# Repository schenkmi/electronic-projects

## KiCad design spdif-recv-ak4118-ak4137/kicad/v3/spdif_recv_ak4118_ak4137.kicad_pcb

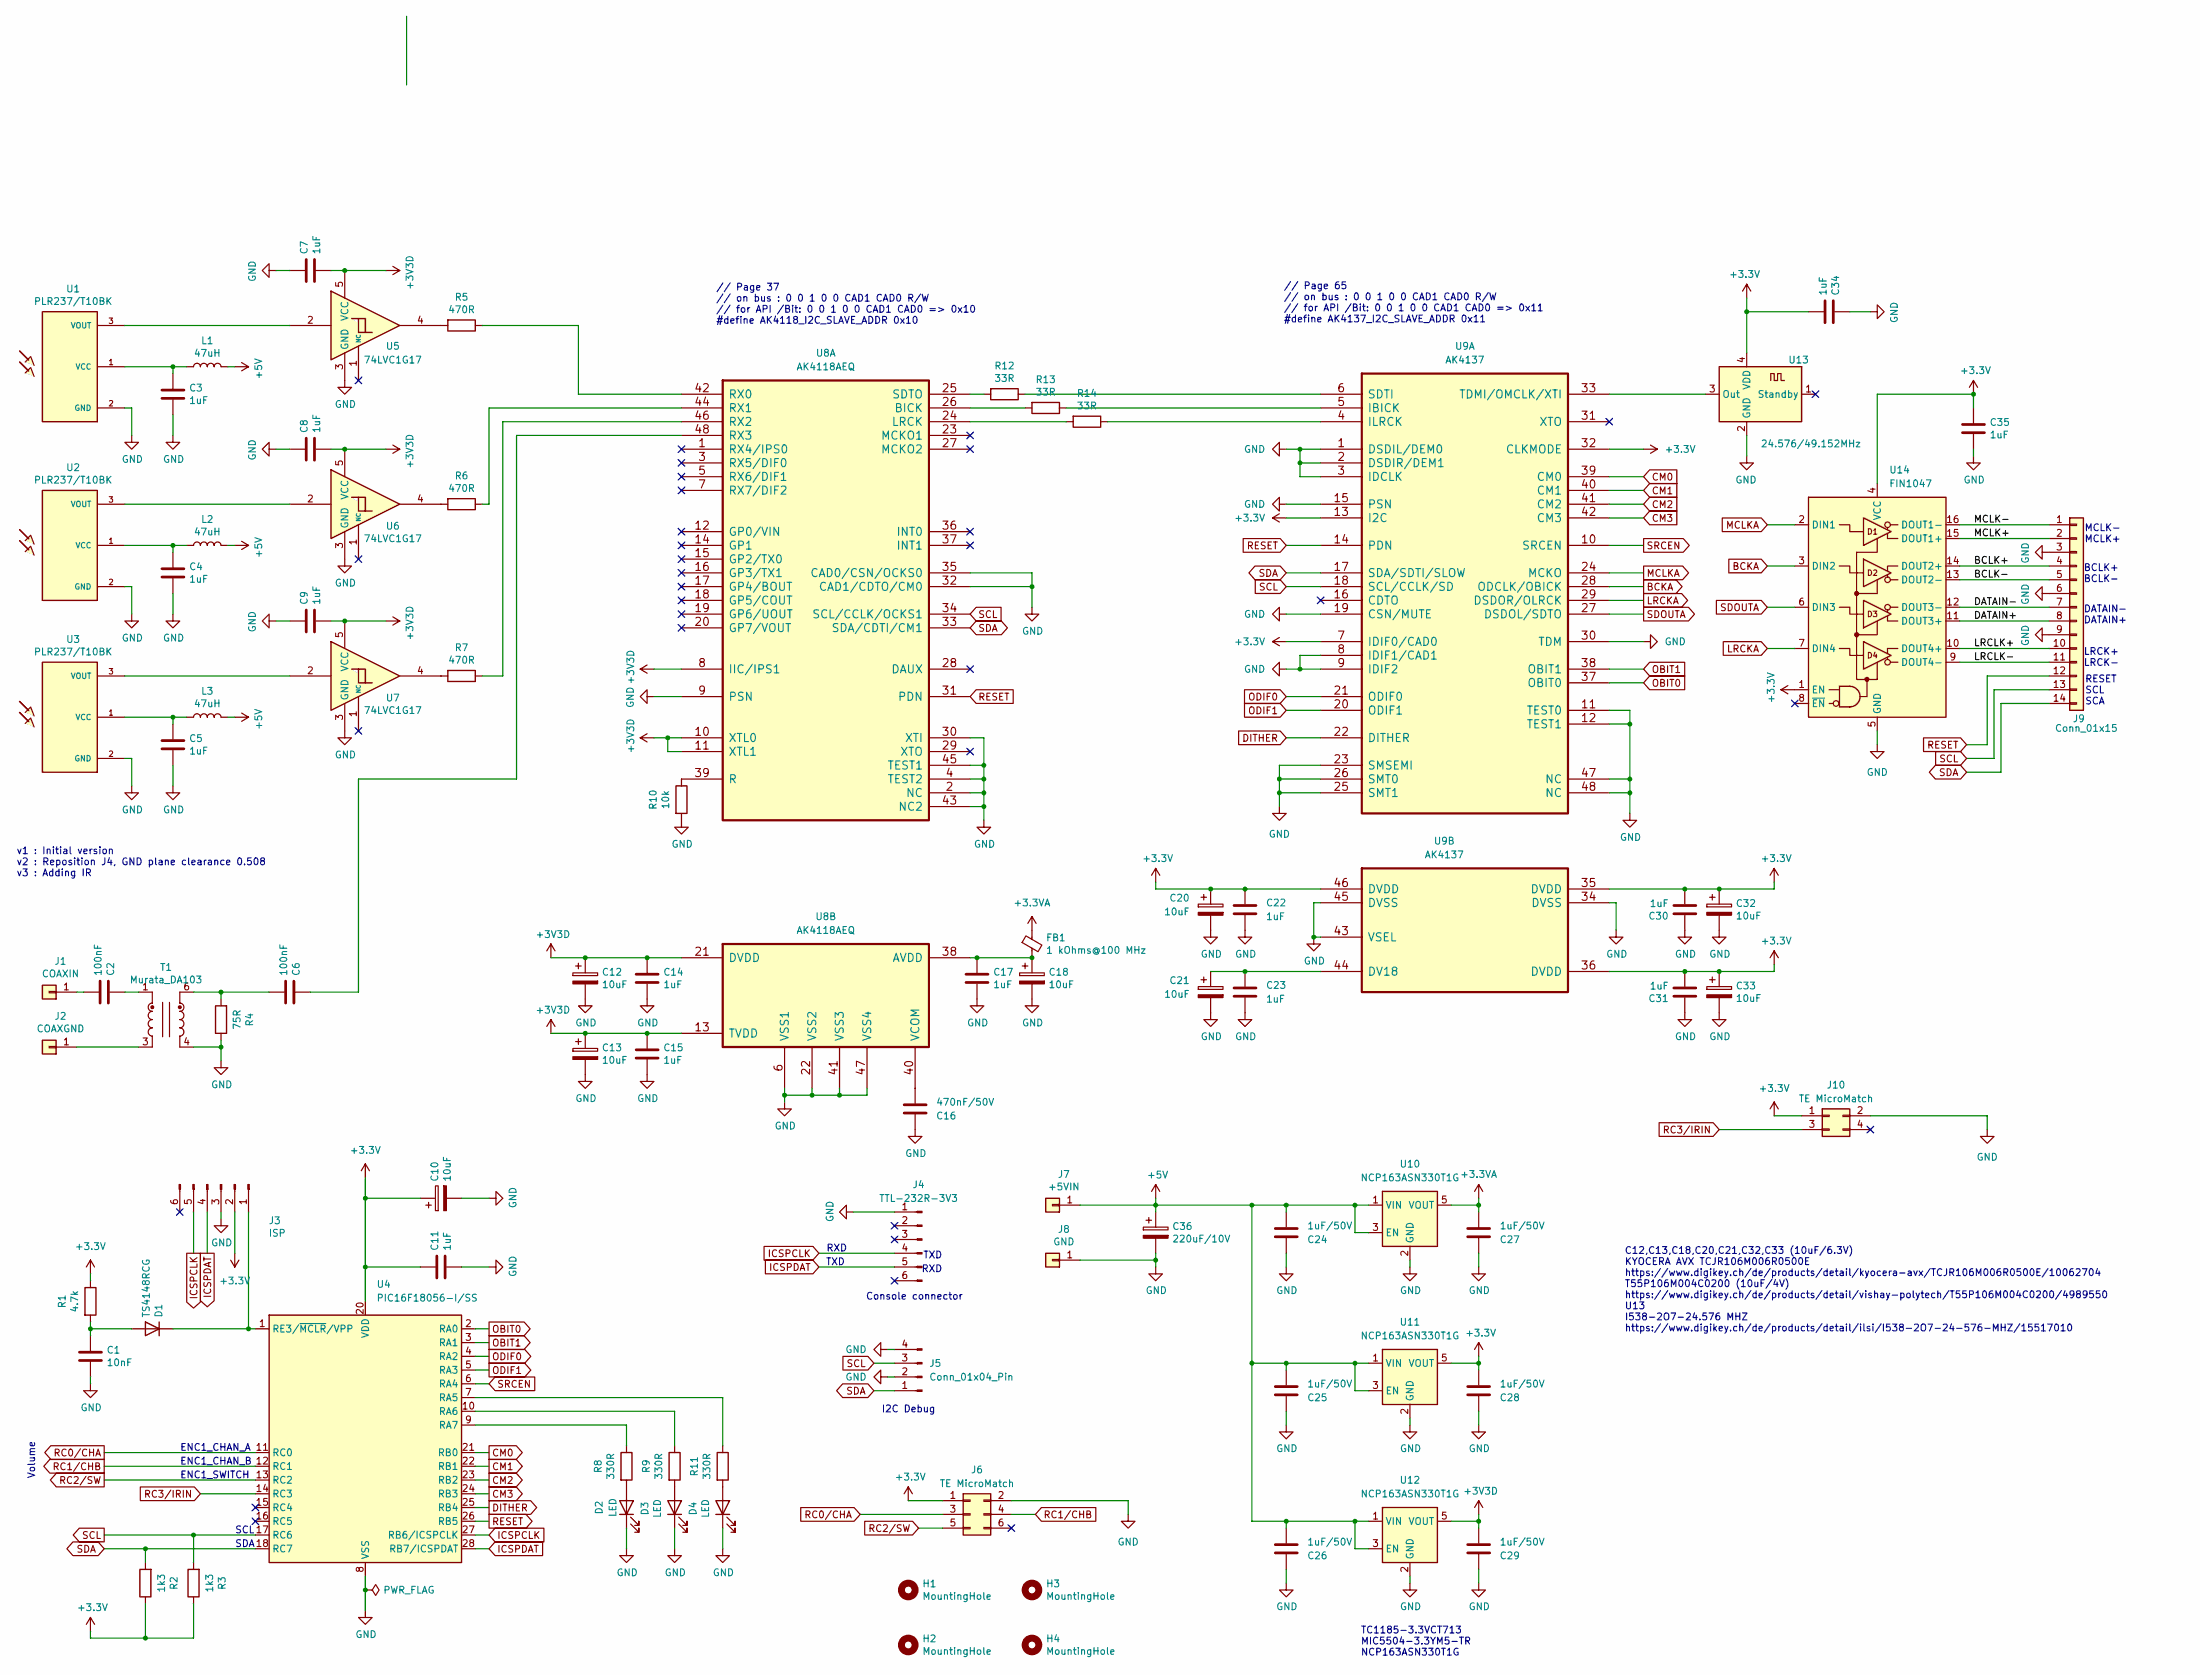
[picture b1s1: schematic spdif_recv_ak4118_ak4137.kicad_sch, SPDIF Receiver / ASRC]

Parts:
C1: 10nF; C_0603_1608Metric_Pad1.08x0.95mm_HandSolder
C2, C6: 100nF; C_0603_1608Metric_Pad1.08x0.95mm_HandSolder
C3, C4, C5, C7, C8, C9, C11, C14, C15, C17, C22, C23, C30, C31, C34, C35: 1uF; C_0603_1608Metric_Pad1.08x0.95mm_HandSolder
C10, C12, C13, C18, C20, C21, C32, C33: 10uF; CP_EIA-2012-12_Kemet-R_HandSolder
C16: 470nF/50V; C_0805_2012Metric_Pad1.18x1.45mm_HandSolder
C24, C25, C26, C27, C28, C29: 1uF/50V; C_0805_2012Metric_Pad1.18x1.45mm_HandSolder
C36: 220uF/10V; CP_Radial_D6.3mm_P2.50mm
D1: TS4148RCG; D_0603_1608Metric_Pad1.05x0.95mm_HandSolder
D2, D3, D4: LED; LED_0603_1608Metric_Pad1.05x0.95mm_HandSolder
FB1: 1 kOhms@100 MHz; C_0603_1608Metric_Pad1.08x0.95mm_HandSolder
H1, H2, H3, H4: MountingHole; MountingHole_3.2mm_M3_Pad_Via
J1: COAXIN; Pin_D1.0mm_L10.0mm
J2: COAXGND; Pin_D1.0mm_L10.0mm
J3: ISP; PinHeader_1x06_P2.54mm_Vertical
J4: TTL-232R-3V3; PinHeader_1x06_P2.54mm_Vertical
J5: Conn_01x04_Pin; PinHeader_1x04_P2.54mm_Vertical
J6: TE MicroMatch; TE_Micro-MaTch_215079-6_2x03_P1.27mm_Vertical
J7: +5VIN; Pin_D1.0mm_L10.0mm
J8: GND; Pin_D1.0mm_L10.0mm
J9: Conn_01x15; TE_Micro-MaTch_1-215079-4_2x07_P1.27mm_Vertical
J10: TE MicroMatch; TE_Micro-MaTch_215079-4_2x02_P1.27mm_Vertical
L1, L2, L3: 47uH; L_0805_2012Metric_Pad1.05x1.20mm_HandSolder
R1: 4.7k; R_0603_1608Metric_Pad0.98x0.95mm_HandSolder
R2, R3: 1k3; R_0603_1608Metric_Pad0.98x0.95mm_HandSolder
R4: 75R; R_0603_1608Metric_Pad0.98x0.95mm_HandSolder
R5, R6, R7: 470R; R_0603_1608Metric_Pad0.98x0.95mm_HandSolder
R8, R9, R11: 330R; R_0603_1608Metric_Pad0.98x0.95mm_HandSolder
R10: 10k; R_0603_1608Metric_Pad0.98x0.95mm_HandSolder
R12, R13, R14: 33R; R_0402_1005Metric_Pad0.72x0.64mm_HandSolder
T1: Murata_DA103; DA100J
U1, U2, U3: PLR237/T10BK; PLR135-T10_PLT133-T10W
U4: PIC16F18056-I/SS; SSOP-28_5.3x10.2mm_P0.65mm
U5, U6, U7: 74LVC1G17; SOT-23-5
U8: AK4118AEQ; LQFP-48_7x7mm_P0.5mm
U9: AK4137; LQFP-48_7x7mm_P0.5mm
U10, U11, U12: NCP163ASN330T1G; SOT-23-5
U13: 24.576/49.152MHz; Oscillator_SMD_EuroQuartz_XO32-4Pin_3.2x2.5mm_RotB_HandSold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
U14: FIN1047; TSSOP-16_4.4x5mm_P0.65mm; Part Number FIN1047MTCX

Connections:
+3.3V: C10.1, C11.1, C20.1, C22.2, C28.2, C30.2, C31.2, C32.1, C33.1, C34.1, C35.1, J3.2, J6.1, J10.1, R1.1, R2.1, R3.1, U4.20 (VDD), U9.7 (IDIF0/CAD0), U9.13 (I2C), U9.32 (CLKMODE), U9.35 (DVDD), U9.36 (DVDD), U9.46 (DVDD), U11.5 (VOUT), U13.4 (VDD), U14.1 (EN), U14.4 (VCC)
+3.3VA: C27.2, FB1.1, U10.5 (VOUT)
+3V3D: C7.1, C8.1, C9.1, C12.1, C13.1, C14.1, C15.1, C29.2, U5.5 (VCC), U6.5 (VCC), U7.5 (VCC), U8.8 (IIC/IPS1), U8.10 (XTL0), U8.11 (XTL1), U8.13 (TVDD), U8.21 (DVDD), U12.5 (VOUT)
+5V: C24.2, C25.2, C26.2, C36.1, J7.1 (Pin_1_1), L1.2, L2.2, L3.2, U10.1 (VIN), U10.3 (EN), U11.1 (VIN), U11.3 (EN), U12.1 (VIN), U12.3 (EN)
/BCLK+: J9.4, U14.14 (DOUT2+)
/BCLK-: J9.5, U14.13 (DOUT2-)
/DATAIN+: J9.8, U14.11 (DOUT3+)
/DATAIN-: J9.7, U14.12 (DOUT3-)
/LRCLK+: J9.10, U14.10 (DOUT4+)
/LRCLK-: J9.11, U14.9 (DOUT4-)
/MCLK+: J9.2, U14.15 (DOUT1+)
/MCLK-: J9.1, U14.16 (DOUT1-)
BCKA: U9.28 (ODCLK/OBICK), U14.3 (DIN2)
CM0: U4.21 (RB0), U9.39 (CM0)
CM1: U4.22 (RB1), U9.40 (CM1)
CM2: U4.23 (RB2), U9.41 (CM2)
CM3: U4.24 (RB3), U9.42 (CM3)
DITHER: U4.25 (RB4), U9.22 (DITHER)
GND: C1.2, C3.1, C4.1, C5.1, C7.2, C8.2, C9.2, C10.2, C11.2, C12.2, C13.2, C14.2, C15.2, C16.1, C17.2, C18.2, C20.2, C21.2, C22.1, C23.1, C24.1, C25.1, C26.1, C27.1, C28.1, C29.1, C30.1, C31.1, C32.2, C33.2, C34.2, C35.2, C36.2, D2.1 (K), D3.1 (K), D4.1 (K), J3.3, J4.1, J5.2, J5.4, J6.2, J8.1 (Pin_1_1), J9.3, J9.6, J9.9, J10.2, R4.1, R10.2, T1.4, U1.2 (GND), U2.2 (GND), U3.2 (GND), U4.8 (VSS), U4.19 (VSS), U5.3 (GND), U6.3 (GND), U7.3 (GND), U8.2 (NC), U8.4 (TEST2), U8.6 (VSS1), U8.9 (PSN), U8.22 (VSS2), U8.30 (XTI), U8.32 (CAD1/CDTO/CM0), U8.35 (CAD0/CSN/OCKS0), U8.41 (VSS3), U8.43 (NC2), U8.45 (TEST1), U8.47 (VSS4), U9.1 (DSDIL/DEM0), U9.2 (DSDIR/DEM1), U9.3 (IDCLK), U9.8 (IDIF1/CAD1), U9.9 (IDIF2), U9.11 (TEST0), U9.12 (TEST1), U9.15 (PSN), U9.19 (CSN/MUTE), U9.23 (SMSEMI), U9.25 (SMT1), U9.26 (SMT0), U9.30 (TDM), U9.34 (DVSS), U9.43 (VSEL), U9.45 (DVSS), U9.47 (NC), U9.48 (NC), U10.2 (GND), U11.2 (GND), U12.2 (GND), U13.2 (GND), U14.5 (GND)
ICSPCLK: J3.5, J4.4, U4.27 (RB6/ICSPCLK)
ICSPDAT: J3.4, J4.5, U4.28 (RB7/ICSPDAT)
LRCKA: U9.29 (DSDOR/OLRCK), U14.7 (DIN4)
MCLKA: U9.24 (MCKO), U14.2 (DIN1)
unnamed: C2.2, T1.1
unnamed: C6.1, R4.2, T1.6
unnamed: C1.1, D1.2 (A), R1.2
unnamed: D1.1 (K), J3.1, U4.1 (RE3/~MCLR/VPP)
unnamed: D2.2 (A), R8.2
unnamed: D3.2 (A), R9.2
unnamed: D4.2 (A), R11.2
unnamed: C2.1, J1.1 (Pin_1_1)
unnamed: J2.1 (Pin_1_1), T1.3
unnamed: R5.2, U5.4
unnamed: R6.2, U6.4
unnamed: R7.2, U7.4
unnamed: C3.2, L1.1, U1.1 (VCC)
unnamed: U1.3 (VOUT), U5.2
unnamed: C4.2, L2.1, U2.1 (VCC)
unnamed: U2.3 (VOUT), U6.2
unnamed: C5.2, L3.1, U3.1 (VCC)
unnamed: U3.3 (VOUT), U7.2
unnamed: R11.1, U4.7 (RA5)
unnamed: R9.1, U4.10 (RA6)
unnamed: R8.1, U4.9 (RA7)
unnamed: R13.2, U8.26 (BICK)
unnamed: R14.2, U8.24 (LRCK)
unnamed: R10.1, U8.39 (R)
unnamed: R5.1, U8.42 (RX0)
unnamed: R6.1, U8.44 (RX1)
unnamed: R7.1, U8.46 (RX2)
unnamed: C6.2, U8.48 (RX3)
unnamed: R12.2, U8.25 (SDTO)
unnamed: C17.1, C18.1, FB1.2, U8.38 (AVDD)
unnamed: C16.2, U8.40 (VCOM)
unnamed: R13.1, U9.5 (IBICK)
unnamed: R14.1, U9.4 (ILRCK)
unnamed: R12.1, U9.6 (SDTI)
unnamed: C21.1, C23.2, U9.44 (DV18)
unnamed: U9.33 (TDMI/OMCLK/XTI), U13.3 (Out)
OBIT0: U4.2 (RA0), U9.37 (OBIT0)
OBIT1: U4.3 (RA1), U9.38 (OBIT1)
ODIF0: U4.4 (RA2), U9.21 (ODIF0)
ODIF1: U4.5 (RA3), U9.20 (ODIF1)
RC0/CHA: J6.3, U4.11 (RC0)
RC1/CHB: J6.4, U4.12 (RC1)
RC2/SW: J6.5, U4.13 (RC2)
RC3/IRIN: J10.3, U4.14 (RC3)
RESET: J9.12, U4.26 (RB5), U8.31 (PDN), U9.14 (PDN)
SCL: J5.3, J9.13, R3.2, U4.17 (RC6), U8.34 (SCL/CCLK/OCKS1), U9.18 (SCL/CCLK/SD)
SDA: J5.1, J9.14, R2.2, U4.18 (RC7), U8.33 (SDA/CDTI/CM1), U9.17 (SDA/SDTI/SLOW)
SDOUTA: U9.27 (DSDOL/SDTO), U14.6 (DIN3)
SRCEN: U4.6 (RA4), U9.10 (SRCEN)

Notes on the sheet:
I2C Debug
// Page 65 // on bus : 0 0 1 0 0 CAD1 CAD0 R/W // for API /Bit: 0 0 1 0 0 CAD1 CAD0 => 0x11 #define AK4137_I2C_SLAVE_ADDR 0x11
ENC1_CHAN_A
SDA
TC1185-3.3VCT713 MIC5504-3.3YM5-TR NCP163ASN330T1G
MCLK- MCLK+
RXD
DATAIN- DATAIN+
BCLK+ BCLK-
// Page 37 // on bus : 0 0 1 0 0 CAD1 CAD0 R/W // for API /Bit: 0 0 1 0 0 CAD1 CAD0 => 0x10 #define AK4118_I2C_SLAVE_ADDR 0x10
Volume
LRCK+ LRCK-
SCL
v1 : Initial version v2 : Reposition J4, GND plane clearance 0.508 v3 : Adding IR
RESET SCL SCA
TXD
C12,C13,C18,C20,C21,C32,C33 (10uF/6.3V) KYOCERA AVX TCJR106M006R0500E https://www.digikey.ch/de/products/detail/kyocera-avx/TCJR106M006R0500E/10062704 T55P106M004C0200 (10uF/4V) https://www.digikey.ch/de/products/detail/vishay-polytech/T55P106M004C0200/4989550 U13 I538-2O7-24.576 MHZ https://www.di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
ENC1_SWITCH
Console connector
ENC1_CHAN_B

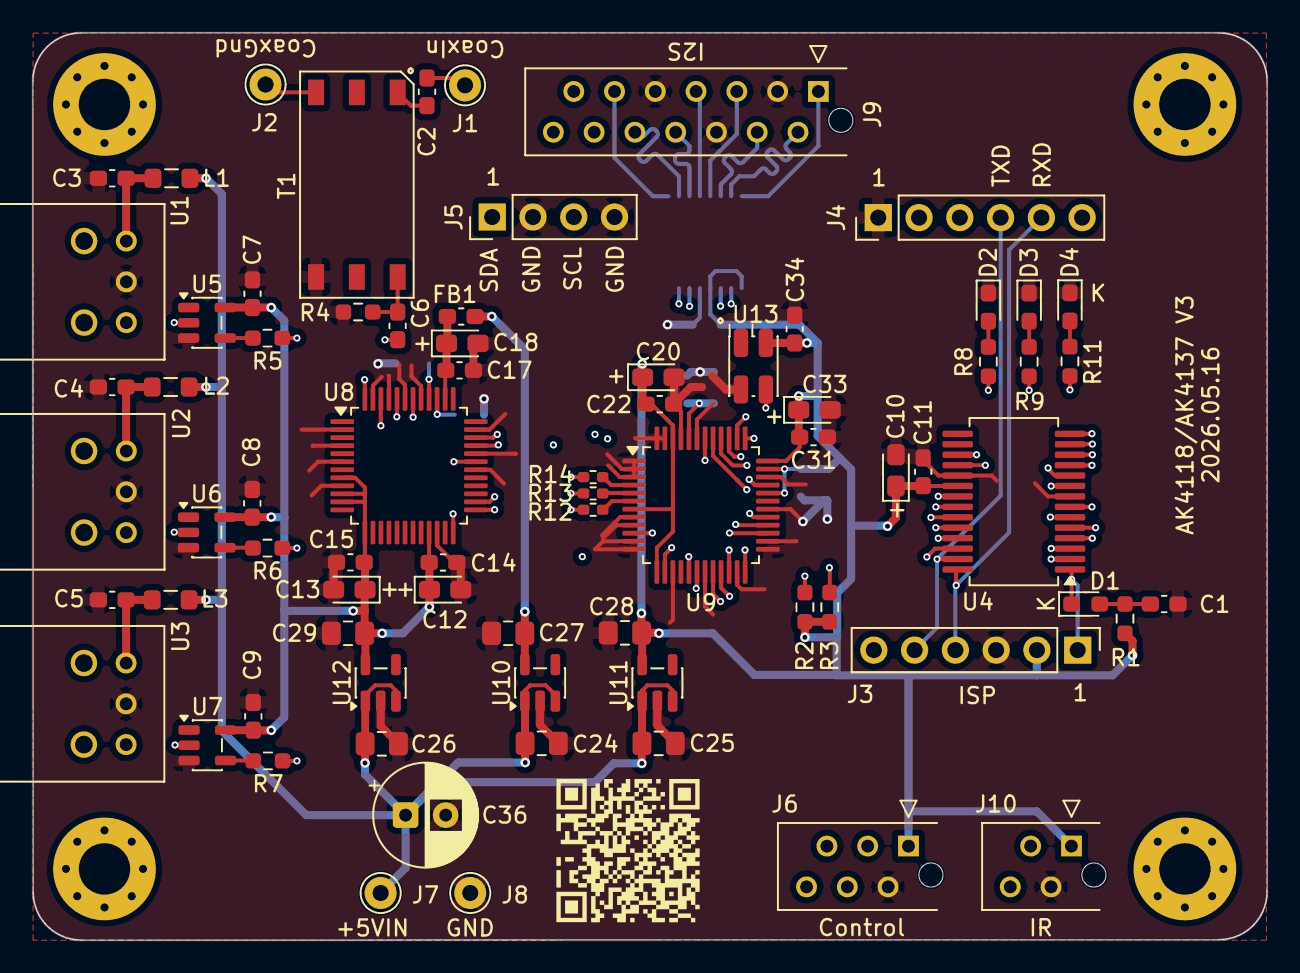
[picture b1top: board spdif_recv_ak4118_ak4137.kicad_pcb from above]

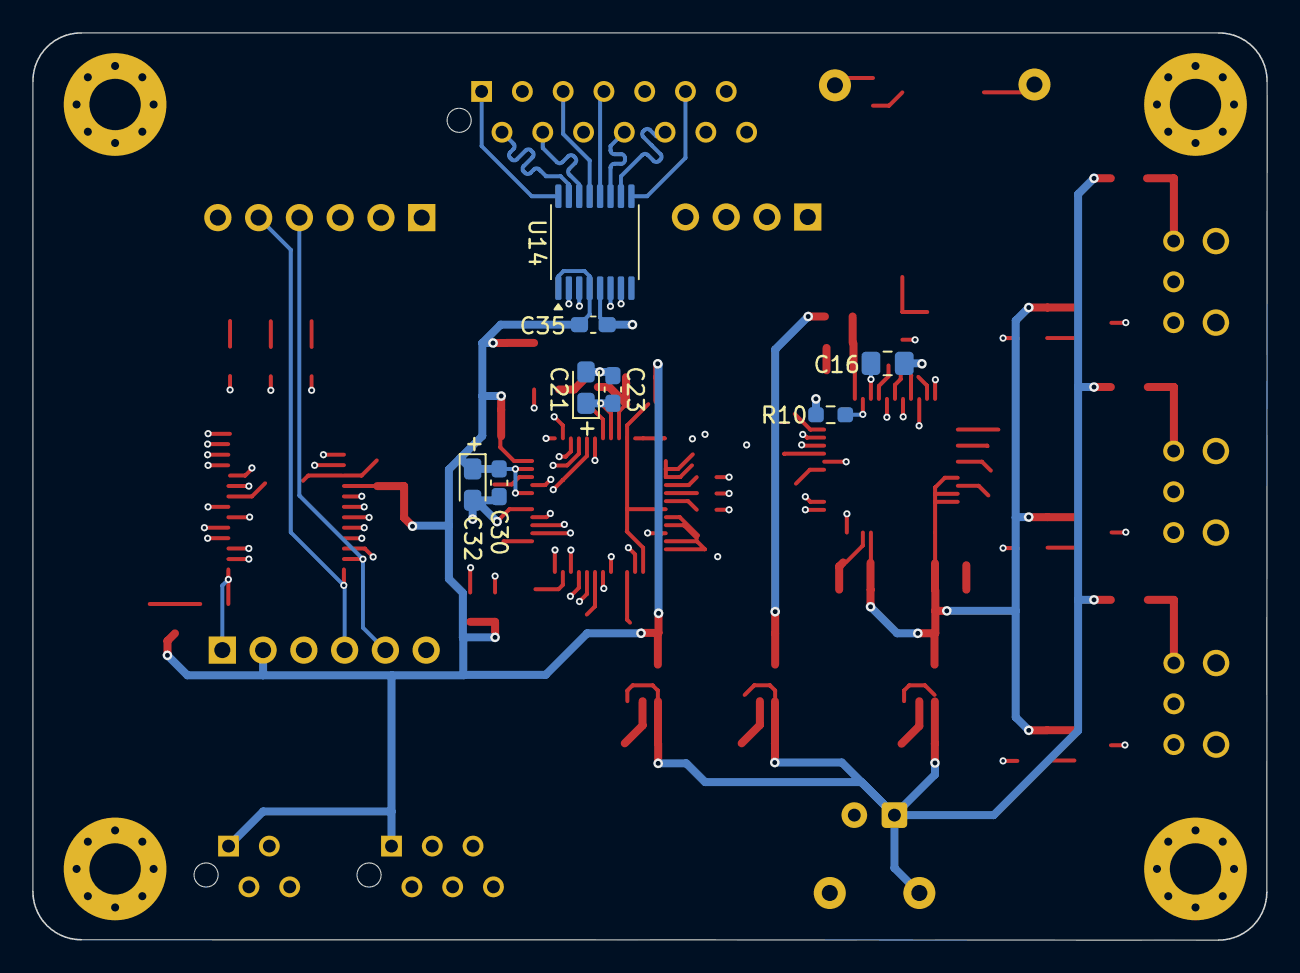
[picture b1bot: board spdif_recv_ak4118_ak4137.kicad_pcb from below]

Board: 4 copper layers, 76.9 x 56.5 mm, 86 parts (8 on the bottom side), 72 nets.

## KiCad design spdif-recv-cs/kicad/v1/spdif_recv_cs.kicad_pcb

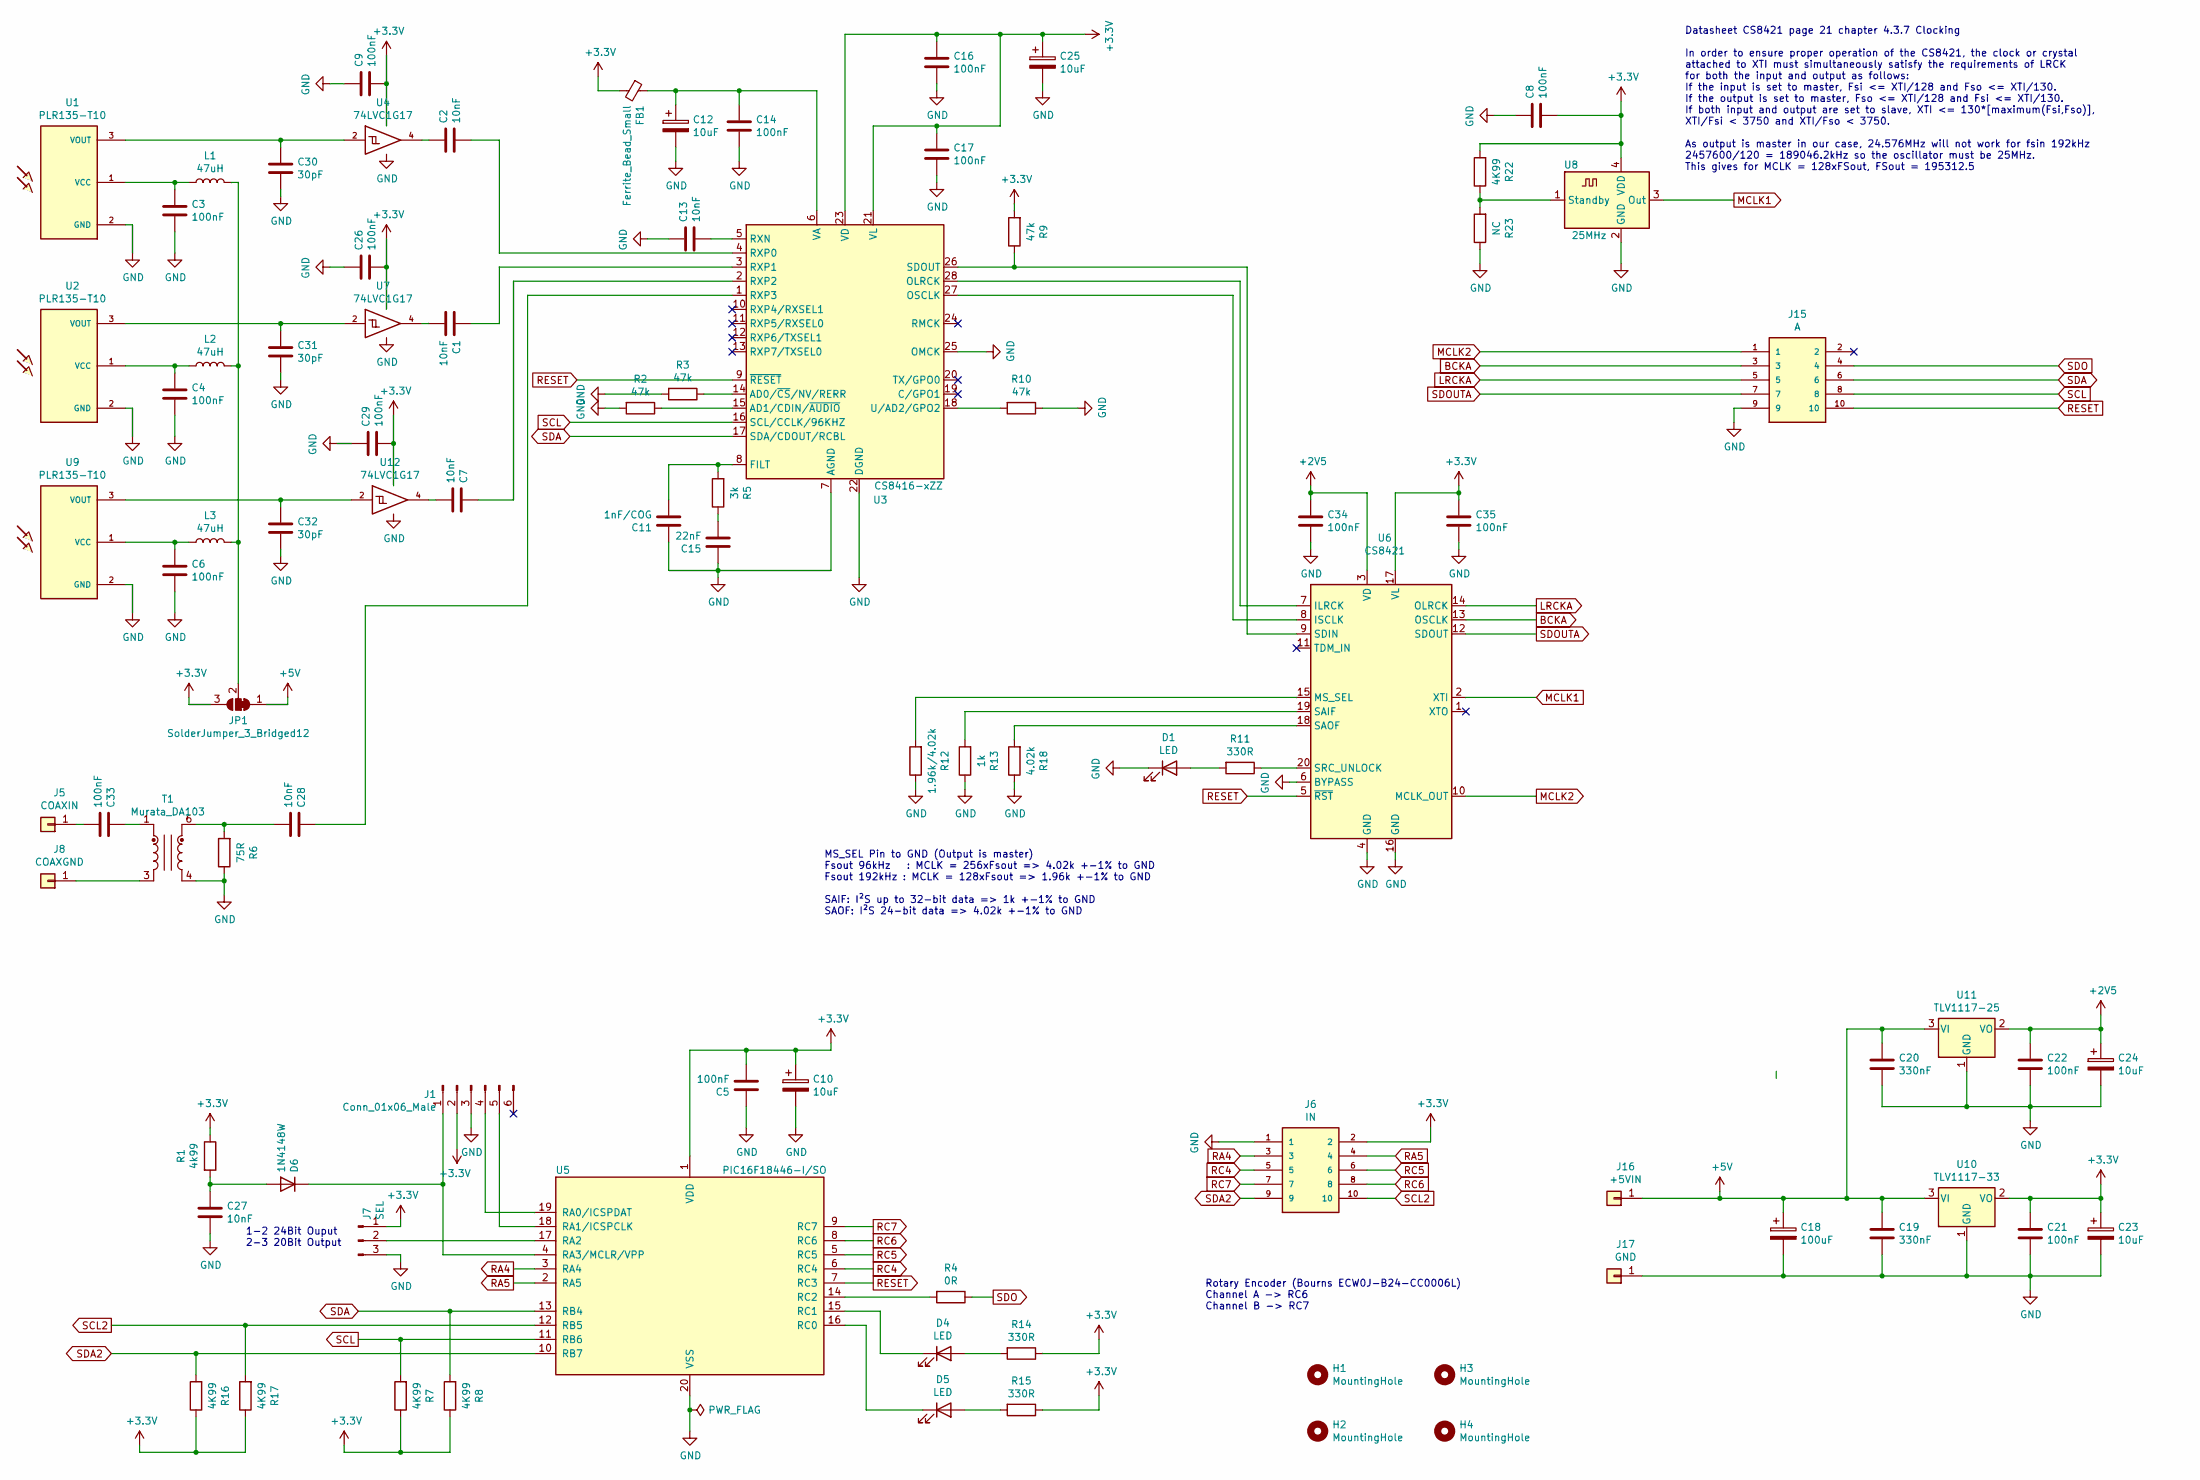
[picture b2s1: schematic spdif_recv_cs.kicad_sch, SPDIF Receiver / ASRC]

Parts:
C1, C2, C7, C13, C27, C28: 10nF; C_0603_1608Metric_Pad1.08x0.95mm_HandSolder
C3, C4, C5, C6, C8, C9, C14, C16, C17, C26, C29, C33, C34, C35: 100nF; C_0603_1608Metric_Pad1.08x0.95mm_HandSolder
C10, C12, C23, C24, C25: 10uF; CP_EIA-3528-21_Kemet-B_Pad1.50x2.35mm_HandSolder
C11: 1nF/COG; C_0603_1608Metric_Pad1.08x0.95mm_HandSolder
C15: 22nF; C_0603_1608Metric_Pad1.08x0.95mm_HandSolder
C18: 100uF; CP_Radial_D8.0mm_P3.50mm
C19, C20: 330nF; C_0805_2012Metric_Pad1.18x1.45mm_HandSolder
C21, C22: 100nF; C_0805_2012Metric_Pad1.18x1.45mm_HandSolder
C30, C31, C32: 30pF; C_0603_1608Metric_Pad1.08x0.95mm_HandSolder
D1, D4, D5: LED; LED_0805_2012Metric_Pad1.15x1.40mm_HandSolder
D6: 1N4148W; D_SOD-123
FB1: Ferrite_Bead_Small; C_0603_1608Metric_Pad1.08x0.95mm_HandSolder
H1, H2, H3, H4: MountingHole; MountingHole_3.2mm_M3
J1: Conn_01x06_Male; PinHeader_1x06_P2.54mm_Vertical
J5: COAXIN; Pin_D1.0mm_L10.0mm
J6: IN; TE_CONN_RCPT_10POS_0.1_TIN_PCB
J7: SEL; PinHeader_1x03_P2.54mm_Vertical
J8: COAXGND; Pin_D1.0mm_L10.0mm
J15: A; TE_CONN_RCPT_10POS_0.1_TIN_PCB
J16: +5VIN; Pin_D1.0mm_L10.0mm
J17: GND; Pin_D1.0mm_L10.0mm
JP1: SolderJumper_3_Bridged12; SolderJumper-3_P1.3mm_Bridged12_RoundedPad1.0x1.5mm_NumberL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
L1, L2, L3: 47uH; L_0805_2012Metric_Pad1.05x1.20mm_HandSolder
R1: 4k99; R_0603_1608Metric_Pad0.98x0.95mm_HandSolder
R2, R3, R9, R10: 47k; R_0603_1608Metric_Pad0.98x0.95mm_HandSolder
R4: 0R; R_0603_1608Metric_Pad0.98x0.95mm_HandSolder
R5: 3k; R_0603_1608Metric_Pad0.98x0.95mm_HandSolder
R6: 75R; R_0603_1608Metric_Pad0.98x0.95mm_HandSolder
R7, R8, R16, R17, R22: 4K99; R_0603_1608Metric_Pad0.98x0.95mm_HandSolder
R11, R14, R15: 330R; R_0603_1608Metric_Pad0.98x0.95mm_HandSolder
R12: 1.96k/4.02k; R_0603_1608Metric_Pad0.98x0.95mm_HandSolder
R13: 1k; R_0603_1608Metric_Pad0.98x0.95mm_HandSolder
R18: 4.02k; R_0603_1608Metric_Pad0.98x0.95mm_HandSolder
R23: NC; R_0603_1608Metric_Pad0.98x0.95mm_HandSolder
T1: Murata_DA103; DA100J
U1, U2, U9: PLR135-T10; PLR135-T10_PLT133-T10W
U3: CS8416-xZZ; TSSOP-28_4.4x9.7mm_P0.65mm
U4, U7, U12: 74LVC1G17; SOT-23-5
U5: PIC16F18446-I/SO; SOIC-20W_7.5x12.8mm_P1.27mm
U6: CS8421; TSSOP-20_4.4x6.5mm_P0.65mm
U8: 25MHz; Oscillator_SMD_EuroQuartz_XO91-4Pin_7.0x5.0mm_HandSoldering
U10: TLV1117-33; SOT-223-3_TabPin2
U11: TLV1117-25; SOT-223-3_TabPin2

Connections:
+2V5: C22.1, C24.1, C34.1, U6.3 (VD), U11.2 (VO)
+3V3: C5.2, C8.1, C9.1, C10.1, C16.1, C17.1, C21.1, C23.1, C25.1, C26.1, C29.1, C35.1, FB1.2, J1.2, J6.2, J7.1, JP1.3 (B), R1.1, R7.1, R8.1, R9.2, R14.1, R15.1, R16.1, R17.1, R22.2, U3.21 (VL), U3.23 (VD), U4.5 (VCC), U5.1 (VDD), U6.17 (VL), U7.5 (VCC), U8.4 (VDD), U10.2 (VO), U12.5 (VCC)
+5V: C18.1, C19.1, C20.1, J16.1, JP1.1 (A), U10.3 (VI), U11.3 (VI)
BCKA: J15.3, U6.13 (OSCLK)
GND: C3.1, C4.1, C5.1, C6.1, C8.2, C9.2, C10.2, C11.1, C12.2, C13.2, C14.2, C15.1, C16.2, C17.2, C18.2, C19.2, C20.2, C21.2, C22.2, C23.2, C24.2, C25.2, C26.2, C27.2, C29.2, C30.1, C31.1, C32.1, C34.2, C35.2, D1.1 (K), J1.3, J6.1, J7.3, J15.9, J17.1, R2.2, R3.2, R6.1, R10.1, R12.1, R13.1, R18.1, R23.1, T1.4, U1.2 (GND), U2.2 (GND), U3.7 (AGND), U3.22 (DGND), U3.25 (OMCK), U4.3 (GND), U5.20 (VSS), U6.4 (GND), U6.6 (BYPASS), U6.16 (GND), U7.3 (GND), U8.2 (GND), U9.2 (GND), U10.1 (GND), U11.1 (GND), U12.3 (GND)
LRCKA: J15.5, U6.14 (OLRCK)
MCLK1: U6.2 (XTI), U8.3 (Out)
MCLK2: J15.1, U6.10 (MCLK_OUT)
unnamed: C1.1, U7.4
unnamed: C1.2, U3.3 (RXP1)
unnamed: C2.1, U3.4 (RXP0)
unnamed: C2.2, U4.4
unnamed: C3.2, L1.1, U1.1 (VCC)
unnamed: C4.2, L2.1, U2.1 (VCC)
unnamed: C6.2, L3.1, U9.1 (VCC)
unnamed: C7.1, U12.4
unnamed: C7.2, U3.2 (RXP2)
unnamed: C11.2, R5.2, U3.8 (FILT)
unnamed: C12.1, C14.1, FB1.1, U3.6 (VA)
unnamed: C13.1, U3.5 (RXN)
unnamed: C15.2, R5.1
unnamed: C27.1, D6.2 (A), R1.2
unnamed: C28.1, R6.2, T1.6
unnamed: C28.2, U3.1 (RXP3)
unnamed: C30.2, U1.3 (VOUT), U4.2
unnamed: C31.2, U2.3 (VOUT), U7.2
unnamed: C32.2, U9.3 (VOUT), U12.2
unnamed: C33.1, J5.1
unnamed: C33.2, T1.1
unnamed: D1.2 (A), R11.2
unnamed: D4.1 (K), U5.15 (RC1)
unnamed: D4.2 (A), R14.2
unnamed: D5.1 (K), U5.16 (RC0)
unnamed: D5.2 (A), R15.2
unnamed: D6.1 (K), J1.1, U5.4 (RA3/MCLR/VPP)
unnamed: J1.4, U5.19 (RA0/ICSPDAT)
unnamed: J1.5, U5.18 (RA1/ICSPCLK)
unnamed: J7.2, U5.17 (RA2)
unnamed: J8.1, T1.3
unnamed: JP1.2 (C), L1.2, L2.2, L3.2
unnamed: R2.1, U3.15 (AD1/CDIN/~AUDIO)
unnamed: R3.1, U3.14 (AD0/~CS/NV/RERR)
unnamed: R4.2, U5.14 (RC2)
unnamed: R9.1, U3.26 (SDOUT), U6.9 (SDIN)
unnamed: R10.2, U3.18 (U/AD2/GPO2)
unnamed: R11.1, U6.20 (SRC_UNLOCK)
unnamed: R12.2, U6.15 (MS_SEL)
unnamed: R13.2, U6.19 (SAIF)
unnamed: R18.2, U6.18 (SAOF)
unnamed: R22.1, R23.2, U8.1 (Standby)
unnamed: U3.27 (OSCLK), U6.8 (ISCLK)
unnamed: U3.28 (OLRCK), U6.7 (ILRCK)
RA4: J6.3, U5.3 (RA4)
RA5: J6.4, U5.2 (RA5)
RC4: J6.5, U5.6 (RC4)
RC5: J6.6, U5.5 (RC5)
RC6: J6.8, U5.8 (RC6)
RC7: J6.7, U5.9 (RC7)
RESET: J15.10, U3.9 (~RESET), U5.7 (RC3), U6.5 (~RST)
SCL: J15.8, R7.2, U3.16 (SCL/CCLK/96KHZ), U5.11 (RB6)
SCL2: J6.10, R17.2, U5.12 (RB5)
SDA: J15.6, R8.2, U3.17 (SDA/CDOUT/RCBL), U5.13 (RB4)
SDA2: J6.9, R16.2, U5.10 (RB7)
SDO: J15.4, R4.1
SDOUTA: J15.7, U6.12 (SDOUT)

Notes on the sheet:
1-2 24Bit Ouput 2-3 20Bit Output
Rotary Encoder (Bourns ECW0J-B24-CC0006L) Channel A -> RC6 Channel B -> RC7
Datasheet CS8421 page 21 chapter 4.3.7 Clocking In order to ensure proper operation of the CS8421, the clock or crystal attached to XTI must simultaneously satisfy the requirements of LRCK for both the input and output as follows: If the input is set to master, Fsi <= XTI/128 and Fso <= XTI/130. If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
MS_SEL Pin to GND (Output is master) Fsout 96kHz : MCLK = 256xFsout => 4.02k +-1% to GND Fsout 192kHz : MCLK = 128xFsout => 1.96k +-1% to GND SAIF: I²S up to 32-bit data => 1k +-1% to GND SAOF: I²S 24-bit data => 4.02k +-1% to GND

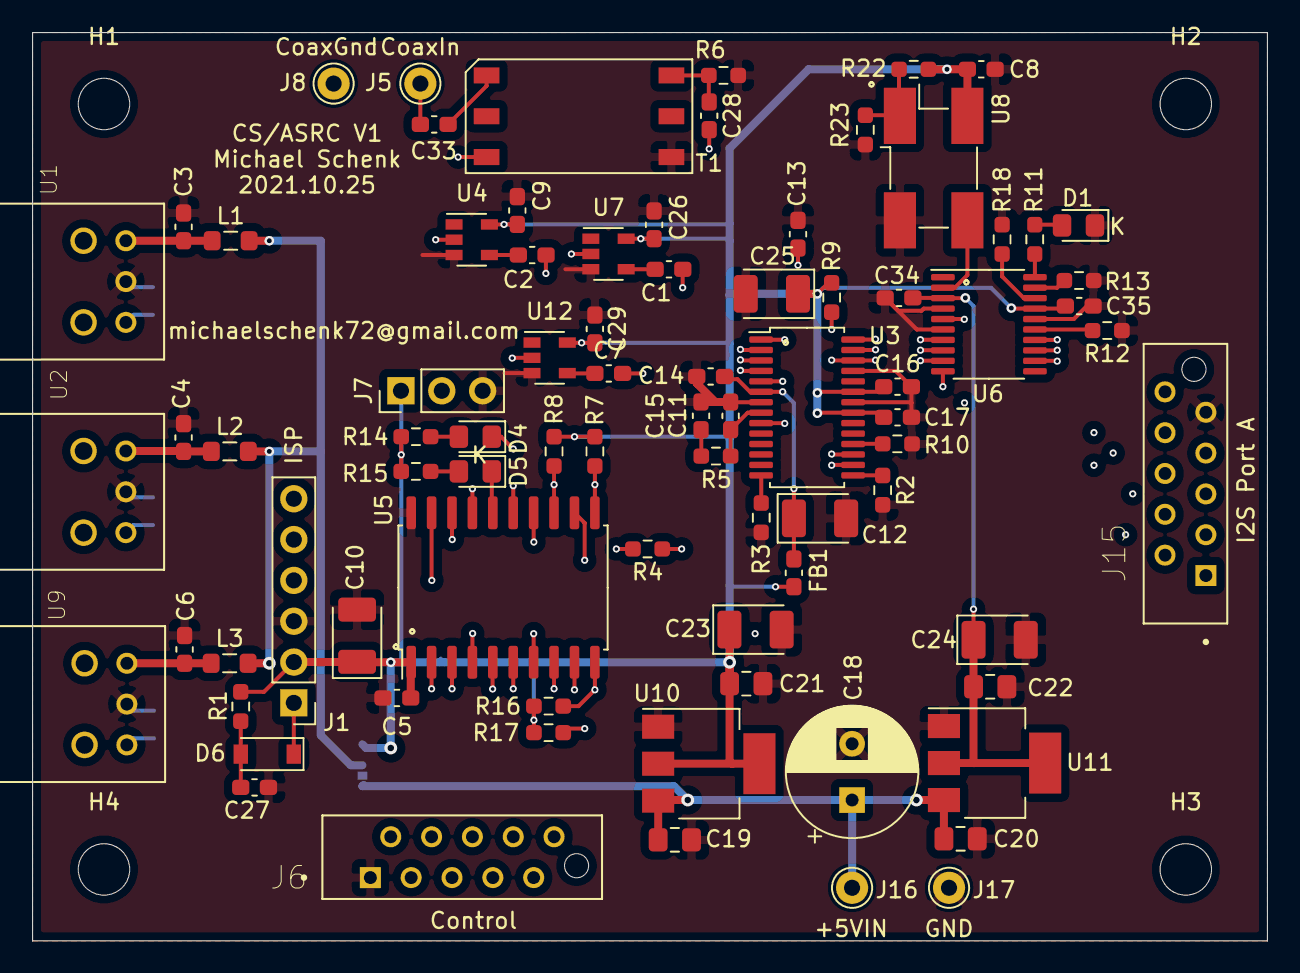
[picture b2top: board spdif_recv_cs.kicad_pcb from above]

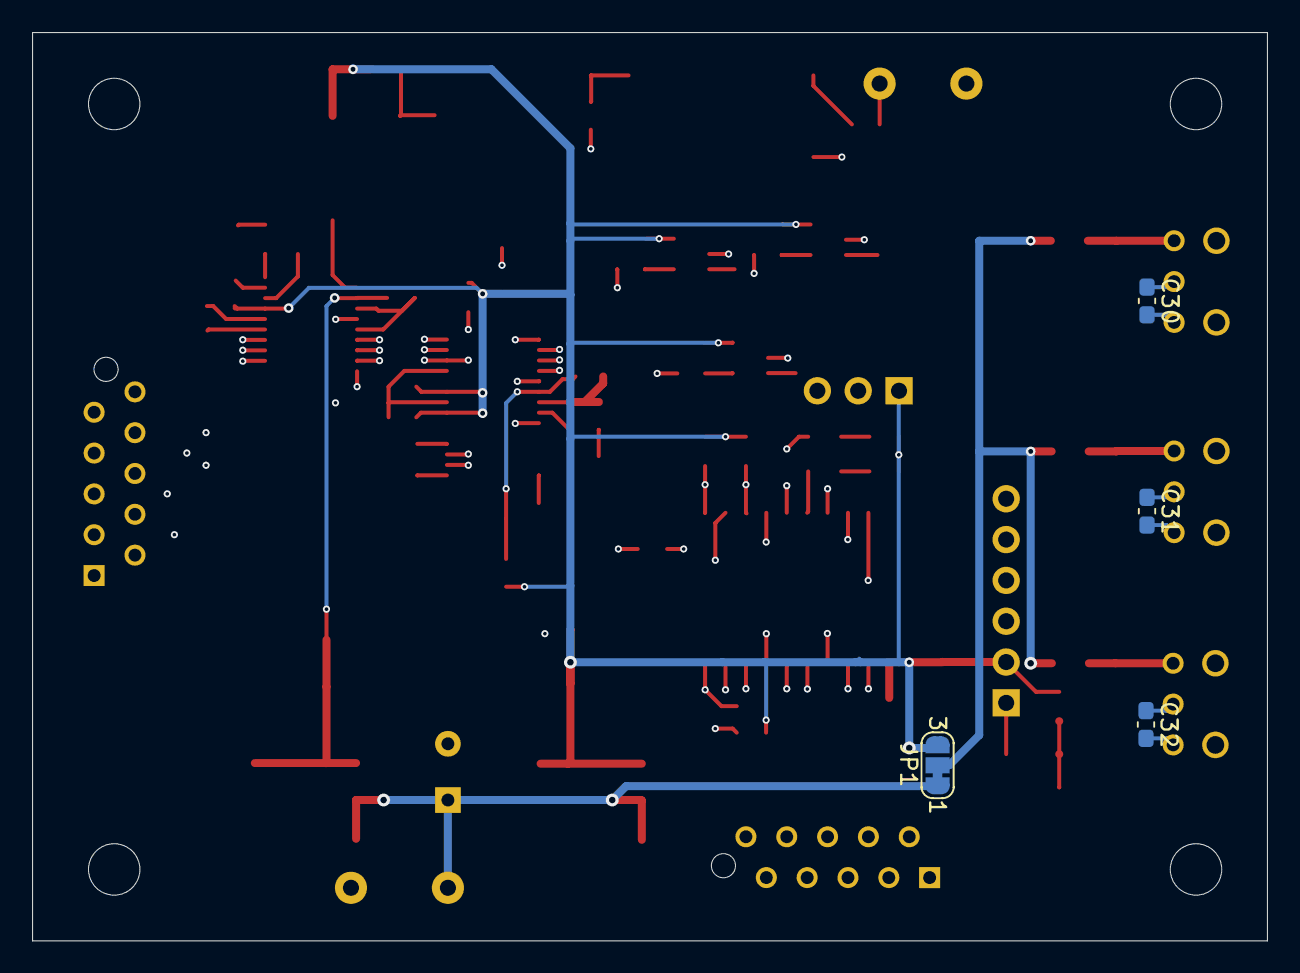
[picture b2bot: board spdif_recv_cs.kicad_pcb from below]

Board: 4 copper layers, 76.8 x 56.5 mm, 89 parts (4 on the bottom side), 65 nets.
